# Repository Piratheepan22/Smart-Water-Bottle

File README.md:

# Smart Drinking Bottle | Consumption Tracking System💧
**A Fully Standalone, Sensor-Fused Hydration Tracker on Custom PCB**

## 📖 Project Overview
Developed as part of the **Embedded Product Design** module under the Department of Electrical and Electronic Engineering, University of Peradeniya, this project is a complete embedded system designed to track daily fluid consumption with high precision.

We challenged the standard IoT approach: instead of relying on Bluetooth and mobile apps, we engineered a device that is **100% autonomous**. It solves the core engineering challenges of fluid tracking—motion artifacts, liquid transparency, and power reliability—through onboard sensor fusion and a custom hardware architecture.

## ⚡ Hardware Architecture (Chip-Down Design)
This project moves beyond modular prototyping. We designed a custom **SMD PCB** where components are reflowed directly for signal integrity and compact integration.

| Subsystem | Component | Implementation Detail |
| :--- | :--- | :--- |
| **MCU** | **ESP32 C3 Mini** | RISC-V core handling logic, I2C coordination, and NVS storage. |
| **Depth Sensor** | **VL53L0X** | Time-of-Flight (ToF) sensor for millimeter-precision level detection. |
| **Motion Sensor** | **BMI270** | Chip-down IMU integration for stability validation. |
| **Touch IC** | **TTP223** | Dedicated Touch Detector IC driving a custom copper electrode on the top of the bottle. |
| **Display** | **0.96" OLED** | Displays hydration stats, time, date, and battery status. |
| **Power** | **Li-Po / TP4056** | External charging circuit with ESP32 ADC voltage monitoring. |

## 🌟 Key Innovations & Features

### 1. The Floating Ring Mechanism (Universal Compatibility)
**The Problem:** Optical sensors (ToF) struggle with clear liquids (light passes through) or reflective liquids (light scatters).
**Our Solution:** We engineered a buoyant, opaque floating ring.
* **Mechanism:** The VL53L0X measures the distance to the *ring*, not the liquid.
* **Benefit:** This makes the bottle **Universal**. It can track water, juice, milk, Medical liquids (that requiring intake measurement) or any other beverage with equal accuracy, regardless of the liquid's color or transparency.
  
Here the image shows the design of Floating - Ring mechanism

### 2. Beyond Hydration: Digital Watch Functionality ⌚
Since this device is designed to sit on a user's desk all day, we integrated full time-keeping features.
* **OLED Dashboard:** The main screen displays the current **Time (HH:MM)** and **Date (DD/MM)** alongside hydration stats.
* **RTC Logic:** Uses a software-based Real-Time Clock to manage date rollovers (automatically resetting the hydration counter after 24Hrs fron limit set time).

### 3. Power Interruption Resilience (Zero Data Loss)
The system is built to handle the real world, where batteries die and devices lose power.
* **Non-Volatile Storage (NVS):** We utilize the ESP32 `Preferences` library to commit data to flash memory.
* **What is Saved:** Current Intake, Daily Goal, and User Settings.
* **Scenario:** If the battery runs out at 2:00 PM with 1.5L consumed, and you charge it back up at 3:00 PM, the device reboots remembering exactly where you left off.

### 4. Custom Capacitive Touch (TTP223)
Instead of mechanical buttons that can wear out or leak, we used a solid-state solution.
* **Hardware:** A **TTP223** Touch Detector IC is mounted on the PCB, connected to a copper pour acting as the sensor pad.
* **Tuning:** The sensitivity is tuned (via capacitor selection) to detect touches *through* the 3D-printed enclosure, offering a sleek, button-less experience.

## 🧠 The "Stability-First" Logic Algorithm
The code implements a Finite State Machine (FSM) that prevents false readings caused by fluid dynamics (sloshing).

### Phase 1: Motion Gating (The BMI270 Watchdog)
The system polls the IMU every 20ms using a **Madgwick Filter** to calculate Pitch and Roll.
* **Tilt Threshold:** If the bottle is tilted > `10.0°` (configurable), measurements are blocked.
* **Motion Detection:** If acceleration vectors deviate from 1G (gravity), the system flags the state as `Unstable`.

### Phase 2: Hysteresis (The 15-Second Rule)

1.  **Stop Detected:** When the bottle becomes upright and still, a timer starts.
2.  **The Wait:** The system waits for a strict `STABILITY_WAIT_MS` of **15,000ms (15 seconds)**.
3.  **Re-Verification:** After 15 seconds, the code checks the IMU one last time. If the bottle moved *at all* during that window, the process aborts.

### Phase 3: Statistical Sampling (The 10-Second Scan)
Once stability is confirmed, the VL53L0X doesn't just take *one* reading. It enters a sampling loop:
* **Duration:** It scans the water level for **10,000ms (10 seconds)**.
* **Filtering:** It captures `MAX_SAMPLES` and calculates the mean.
* **Outlier Removal:** Any sample deviating more than `10mm` from the mean is discarded.
* **Result:** The final "Cleaned Average" is used to calculate volume.

## 🧮 Volume Calculation & Physics
The firmware calculates volume based on the differential distance to the liquid surface.

* **Refill vs. Drink Logic:**
    * **Consumption:** If distance *increases* (`Current > Last` by > 0.05dm), water was consumed.
    * **Refill:** If distance *decreases* significantly (`Current < Last` by > 0.2dm), the system detects a refill event and resets the baseline without adding to the "Consumed" total.
* **Unit Conversion:**
    * `Cross Section Area` = 0.4225 dm²
    * `Volume Delta` = `Delta Distance` × `Cross Section Area`

## ⚙️ Operating Modes

| Mode | Functionality | Reset Behavior |
| :--- | :--- | :--- |
| **Mode 1: Daily Goal** | Tracks intake against a user-set limit (e.g., 2.5L). | **Automatic:** Resets intake to 0 after 24 Hours from the time when limit set. |
| **Mode 2: Continuous** | Unrestricted tracking (e.g., for weekly stats). | **Manual:** Only resets when user requests. |

## 🎮 User Interface & Controls
Interaction is handled entirely through the **capacitive touch pad embedded in the bottle cap**. The system detects context-sensitive tap patterns depending on whether the device is in normal use or initial setup (after a reset or power loss).

Input Handling Algorithm: The firmware utilizes a non-blocking debounce routine with a 300ms accumulation window (gab between touches for detect multiple touch actions). Input actions are only triggered once the input line has remained idle for the full duration of the window, ensuring reliable distinction between Single, Double, and Triple tap events without false positives.

### 1. Initial Setup Mode (Time & Date)
*Triggered automatically after a hard reset or power loss(power off).*

| Gesture | Action | Function |
| :--- | :--- | :--- |
| **Single Tap (1x)** | **Increment** | Increases the current flashing value (Year -> Month -> Day -> Hour -> Minute). |
| **Double Tap (2x)** | **Next Step** | Saves the current value and moves to the next field. |
| **Triple Tap (3x)** | **Back** | Returns to the previous field to correct a mistake. |

### 2. Normal Operation Mode
*Standard daily usage.*

| Gesture | Action | Function |
| :--- | :--- | :--- |
| **Single Tap (1x)** | **Increment / Nav** | Increases setting values or navigates screens. |
| **Double Tap (2x)** | **Wake / Confirm** | Wakes OLED from sleep. Confirms selection. Enters "Set Goal" mode. |
| **Triple Tap (3x)** | **Switch Mode** | Toggles between **Daily Goal Mode** and **Continuous Tracking Mode**. |
| **Idle (2 sec)** | **Timeout** | If no input is detected, the screen sleeps or cancels the current action. |

## 👥 Team members
**Product Design Team:**
* **Piratheepan Mathivathanan**
* **E. M. T. L. K. Ekanayake**  
* **Sarusan Sivanesan**

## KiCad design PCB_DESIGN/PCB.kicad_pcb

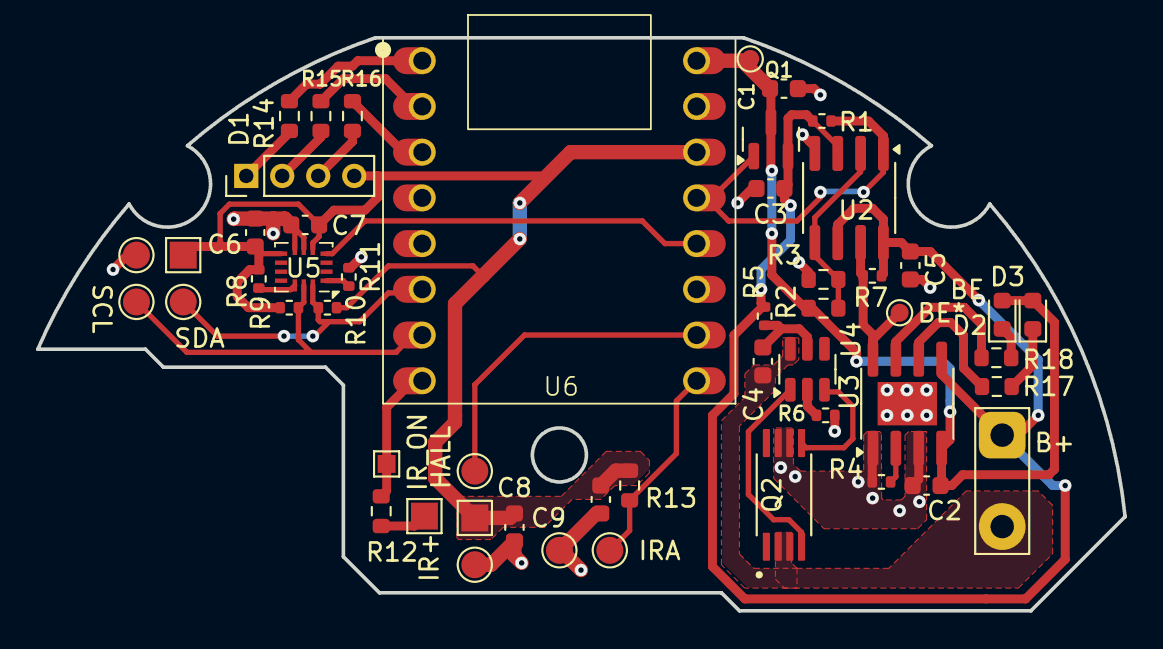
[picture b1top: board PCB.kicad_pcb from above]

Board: 2 copper layers, 60.4 x 31.8 mm, 51 parts (0 on the bottom side), 32 nets.

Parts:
C1, C3, C9: 10u; C_0603_1608Metric
C2, C4, C5, C6, C7, C8: 100n; C_0603_1608Metric
D1: LED_RGBA; PinHeader_1x04_P2.00mm_Vertical
D2: RED_LED; LED_0603_1608Metric
D3: GREEN_LED; LED_0603_1608Metric
J1: Battery_Connector; TestPoint_2Pads_Pitch5.08mm_Drill1.3mm
J3, J4, J19, J22, J23, J24, J25: Conn_01x01_Pin; TestPoint_Pad_D1.5mm
J7: Conn_01x01_Pin; TestPoint_Pad_1.0x1.0mm
J8, J18, J21: Conn_01x01_Pin; TestPoint_Pad_1.5x1.5mm
J9, J12: Conn_01x01_Pin; TestPoint_Pad_D1.0mm
Q1: AO3400A; SOT-23
Q2: FS8205A
R1, R7, R8, R11: 100k; R_0402_1005Metric
R2: 2k2; R_0603_1608Metric
R3: 82k; R_0603_1608Metric
R4: 2k; R_0402_1005Metric
R5: 100; R_0402_1005Metric
R6: 1k; R_0402_1005Metric
R9, R10: 2k2; R_0402_1005Metric
R12: 150; R_0603_1608Metric
R13: 10k; R_0603_1608Metric
R14, R15, R16: 220; R_0603_1608Metric
R17, R18: 1k; R_0603_1608Metric
U2: LM393; SOIC-8_3.9x4.9mm_P1.27mm
U3: TP4056-42-ESOP8; SOIC-8-1EP_3.9x4.9mm_P1.27mm_EP2.41x3.3mm
U4: DW01A; SOT-23-6
U5: BMI270; Bosch_LGA-14_3x2.5mm_P0.5mm
U6: ESP32_C3_SuperMini

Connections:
+3.3V: C6.1, C7.1, C8.1, C9.1, D1.4 (A), J18.1, J21.1, R8.2, R9.2, R10.2, R13.1, U5.5 (VDDIO), U5.8 (VDD), U6.14 (3V3)
+BATT: C3.1, C5.1, J1.1, Q1.2 (S), R1.2, R5.1, R7.2, U2.3 (+), U2.6 (-), U2.8 (V+), U3.5 (BAT)
-BATT: C4.1, J1.2, Q2.2, Q2.3, U4.6 (GND)
/IR: J8.1, R12.2
ADR: R11.2, U5.1 (SDO)
Batt_En: Q1.1 (G), R1.1, U2.1, U6.13 (GPIO4)
Batt_En*: J9.1, R7.1, U2.7, U3.8 (CE)
GND: C1.2, C2.1, C3.2, C5.2, C6.2, C7.2, C8.2, C9.2, J19.1, J22.1, J25.1, Q2.6, Q2.7, R3.2, R4.2, R6.2, R11.1, U2.4 (V-), U3.1 (TEMP), U3.3 (GND), U3.9 (EPAD), U5.6 (GNDIO), U5.7 (GND), U6.15 (GND)
Hall_Out: J23.1, U6.10 (GPIO1)
IMU_INT1: U5.4 (INT1), U6.12 (GPIO3)
IMU_SCL: J3.1, R9.1, U5.13 (SCx), U6.7 (GPIO20)
IMU_SDA: J4.1, R10.1, U5.14 (SDx), U6.6 (GPIO10)
IR_ADC: J24.1, R13.2, U6.9 (GPIO0)
IR_ON: J7.1, R12.1, U6.8 (GPIO21)
unnamed: D1.3 (BK), R16.2
unnamed: D1.2 (GK), R15.2
unnamed: D1.1 (RK), R14.2
unnamed: D2.1 (K), R18.1
unnamed: D3.1 (K), R17.1
unnamed: R4.1, U3.2 (PROG)
unnamed: R18.2, U3.7 (~CHRG)
unnamed: R17.2, U3.6 (~STDBY)
unnamed: R6.1, U4.2 (CS)
unnamed: Q2.5, U4.3 (OC)
unnamed: Q2.4, U4.1 (OD)
unnamed: C4.2, R5.2, U4.5 (VCC)
unnamed: R8.1, U5.12 (CSB)
PWM_B: R16.1, U6.3 (GPIO7)
PWM_G: R15.1, U6.2 (GPIO6)
PWM_R: R14.1, U6.1 (GPIO5)
VCC_Sense: R2.2, R3.1, U2.2 (-), U2.5 (+)
Vin: C1.1, C2.2, D2.2 (A), D3.2 (A), J12.1, Q1.3 (D), R2.1, U3.4 (V_{CC}), U6.16 (Vin)

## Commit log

2025-12-30 Add files via upload
    initial commit
2025-12-30 Create CNAME
2025-12-30 Update CNAME
2026-02-03 Initialize README with project details and features
    Added detailed project content
2026-02-03 Revise project overview
    updated
2026-02-03 Revise project overview in README.md
    Updated
2026-02-03 updated details of pcb and 3d design
2026-02-03 Enhance README
2026-02-03 Revise README for algorithm and UI controls clarity
    Updated the README to enhance clarity on the Stability-First Logic Algorithm and user interface controls.
2026-02-03 page updated
2026-02-03 updating pcb and codes
2026-02-04 page-updated
